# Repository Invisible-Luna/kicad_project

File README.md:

# kicad_project

#Pravallika Saladi <br />
##119EC0013 <br />

Project done as part of Prototyping Lab. <br />
Project Name: Fan Dimmer with PWM <br />
Software used: KiCad <br />
Files included: .sch, .pcb, gerber files, Bill of Materials (BOM) in .csv, .xlsv formats, related libraries, footprints, symbols files. <br />
Final Report and Presentation is also uploaded. <br />

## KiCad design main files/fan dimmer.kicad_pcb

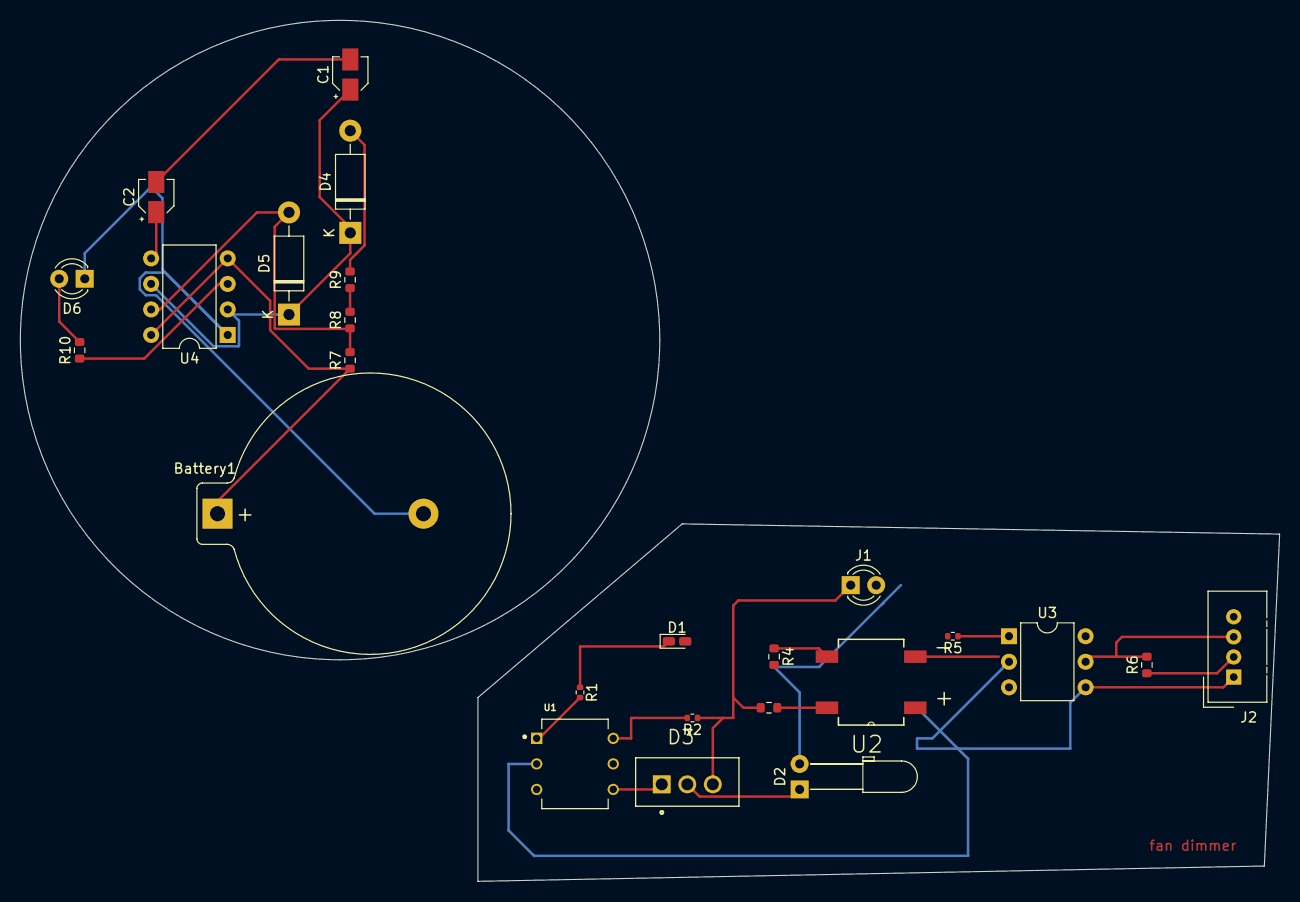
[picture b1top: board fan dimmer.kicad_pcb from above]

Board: 2 copper layers, 125.3 x 85.7 mm, 25 parts (0 on the bottom side), 22 nets.

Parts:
Battery1: 9v; BatteryHolder_Keystone_107_1x23mm
C1: 47nF; CP_Elec_3x5.3
C2: 10nF; CP_Elec_3x5.3
D1: LED; LED_0603_1608Metric_Castellated
D2: LED; LED_D3.0mm_Horizontal_O6.35mm_Z2.0mm
D3: BTA16-600CW3G; TO254P1028X482X1968-3
D4, D5: 1N4007; D_DO-41_SOD81_P10.16mm_Horizontal
D6: LED; LED_D3.0mm_Clear
J1: Conn_01x02_Male; LED_D3.0mm_Clear
J2: Conn_01x04_Male; NS-Tech_Grove_1x04_P2mm_Vertical
R1, R2, R5: 1k; R_0402_1005Metric
R3, R4: 30k; R_0603_1608Metric
R6, R7, R9: 10k; R_0603_1608Metric
R8: 100k; R_0603_1608Metric
R10: 220; R_0603_1608Metric
U1: MOC3021; DIP762W45P254L889H508Q6
U2: DF10S; SOT508P985X260-4N
U3: 4N25; DIP-6_W7.62mm
U4: LM555xN; DIP-8_W7.62mm

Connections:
GND: Battery1.2, C1.2, C2.2, D6.1, J2.1, U1.2, U2.1, U3.2, U3.4, U4.1
unnamed: Battery1.1, R7.1, U4.4, U4.8
unnamed: C1.1, D4.1, D5.1, U4.2, U4.6
unnamed: C2.1, U4.5
unnamed: D1.1, R1.1
unnamed: D2.1, D3.2
unnamed: D2.2, J1.2, R4.2
unnamed: D3.1, U1.4
unnamed: D3.3, J1.1, R2.1, R3.2
unnamed: D4.2, R9.2
unnamed: D5.2, R7.2, R8.1, U4.7
unnamed: D6.2, R10.2
unnamed: J2.2, R6.1
unnamed: J2.3, R6.2, U3.5
unnamed: R1.2, U1.1
unnamed: R2.2, U1.6
unnamed: R3.1, U2.4
unnamed: R4.1, U2.3
unnamed: R5.1, U3.1
unnamed: R5.2, U2.2
unnamed: R8.2, R9.1
PWM: D1.2, J2.4, R10.1, U4.3

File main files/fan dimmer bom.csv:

"Id";"Designator";"Package";"Quantity";"Designation";"Supplier and ref";
1;"Battery1";"BatteryHolder_Keystone_107_1x23mm";1;"9v";;;
2;"C2";"CP_Elec_3x5.3";1;"10nF";;;
3;"C1";"CP_Elec_3x5.3";1;"47nF";;;
4;"U4";"DIP-8_W7.62mm";1;"LM555xN";;;
5;"R10";"R_0603_1608Metric";1;"220";;;
6;"R9,R7,R6";"R_0603_1608Metric";3;"10k";;;
7;"R8";"R_0603_1608Metric";1;"100k";;;
8;"J1";"LED_D3.0mm_Clear";1;"Conn_01x02_Male";;;
9;"D6";"LED_D3.0mm_Clear";1;"LED";;;
10;"D5,D4";"D_DO-41_SOD81_P10.16mm_Horizontal";2;"1N4007";;;
11;"U2";"SOT508P985X260-4N";1;"DF10S";;;
12;"U1";"DIP762W45P254L889H508Q6";1;"MOC3021";;;
13;"D3";"TO254P1028X482X1968-3";1;"BTA16-600CW3G";;;
14;"J2";"NS-Tech_Grove_1x04_P2mm_Vertical";1;"Conn_01x04_Male";;;
15;"U3";"DIP-6_W7.62mm";1;"4N25";;;
16;"R5,R2,R1";"R_0402_1005Metric";3;"1k";;;
17;"R4,R3";"R_0603_1608Metric";2;"30k";;;
18;"D2";"LED_D3.0mm_Horizontal_O6.35mm_Z2.0mm";1;"LED";;;
19;"D1";"LED_0603_1608Metric_Castellated";1;"LED";;;

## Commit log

2021-11-12 added bom
2021-11-12 added libraries and footprints of soem components
2021-11-12 gerber file (drill) added
2021-11-12 sch, pcb, bom, netlist etc etc are added
